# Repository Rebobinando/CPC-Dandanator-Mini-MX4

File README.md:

# CPC Dandanator!Mini MX4

## What is this? Why?

Based on the original design from Dandare - CPC Dandanator!Mini, this design proposes the adoption/integration of MX4 connector instead of the Amstrad CPC standard 50 pin edge connector. This version then fits into the many expansion boards available up to now.

This allows for the CPC expansion boards users to enjoy this hardware, together with rest of accessories without the need of unplugging them.

Original design and complete description are available in the [Dandare Website](http://www.dandare.es/Proyectos_Dandare/CPC_Dandanator%21_Mini.html)

More development details are available in [VadeRetro forum](https://www.va-de-retro.com/foros/viewtopic.php?f=63&t=9113) 

## Features

Additionally to the features available in the original design, I added the additional following ones:

- MX4 connector format to fit into CPC expansion boards.
- CPLD is plugged into a socket for easier soldering process by hand.
- Switch for Enable/Disable the accessory instead of button.
- DIP oscillator instead of SMD one.
- Additional switch to switch on /switch off the board.

CPLD programming is fully compatible with original version available at Dandare website.

EEPROM programming original software is also fully compatible. It is available in Dandare website too.

## Bill of materials

|Qty| Component     | Value               |  Package  |
|---|---------------|---------------------|-----------|
| 3 | Capacitor     | 100nF               | SMD C0805 | 
| 2 | Capacitor     | 10uF                | SMD C0805 |
| 2 | Capacitor     | 22pF                | SMD C0805 |
| 1 | Capacitor     | 10nF                | SMD C0805 |
| 1 | IC            | CH340G              | SOP16     |
| 1 | Voltage Reg   | AMS1117-3.3         | SOT223    |
| 1 | MPF           | SST39SF040          | PLCC32    |
| 1 | CPLD          | XC9572XL            | PLCC44    |
| 1 | Oscillator    | 12 MHz              | HC49S     |
| 3 | Resistor      | 10K                 | R805      |
| 1 | USB plug      | Micro USB Type B    | SMD       |
| 1 | pin           | 1x6                 | DIP       |
| 1 | pin           | 1x2                 | DIP       |
| 2 | Button        | 6x6x9 Right Angle   | DIP       |
| 2 | Switch        | MSK-12D19           | DIP       |
| 1 | MX4 connector | DC3-50P Right Angle | DIP       |
| 1 | Socket        | PLCC32              | DIP       |
| 1 | Socket        | PLCC44              | DIP       |

## Board layout

These are the main elements:

All development of this version has been performed with Eagle 8.6.0. Schematics and Board files are available, as well as Gerber files under below license agreement.

This is the board installed onto the CPC expansion board:

PCB screenshot:

## Warning & Disclaimer
If you want to build yourself, please proceed and read carefully all this information. A guide of assembly is available in VadeRetro forum [here](https://www.va-de-retro.com/foros/viewtopic.php?f=63&t=9113) . Bear in mind that all the information in this project is published in good faith and for general information purpose only. I do not make any warranties about the completeness, reliability, and accuracy of this information. Any action you take upon the information you find here, is strictly at your own risk. I will not be liable for any losses and/or damages. In case of doubts, do not hesitate to ask and I will try to help as far as I can!

## Thanks to

- Dandare and the team for carrying out the original (smart & awesome) design of this interface, for giving permission for use and modification of it, and for giving support during the development.

- All the users for VadeRetro forum, who supported the initial batch of units.

Hope we are all enjoying them!

## Redistribution

All development is Public Domain, as the original one. For latest state, please check at [Dandare website](http://www.dandare.es/Proyectos_Dandare/CPC_Dandanator%21_Mini.html)

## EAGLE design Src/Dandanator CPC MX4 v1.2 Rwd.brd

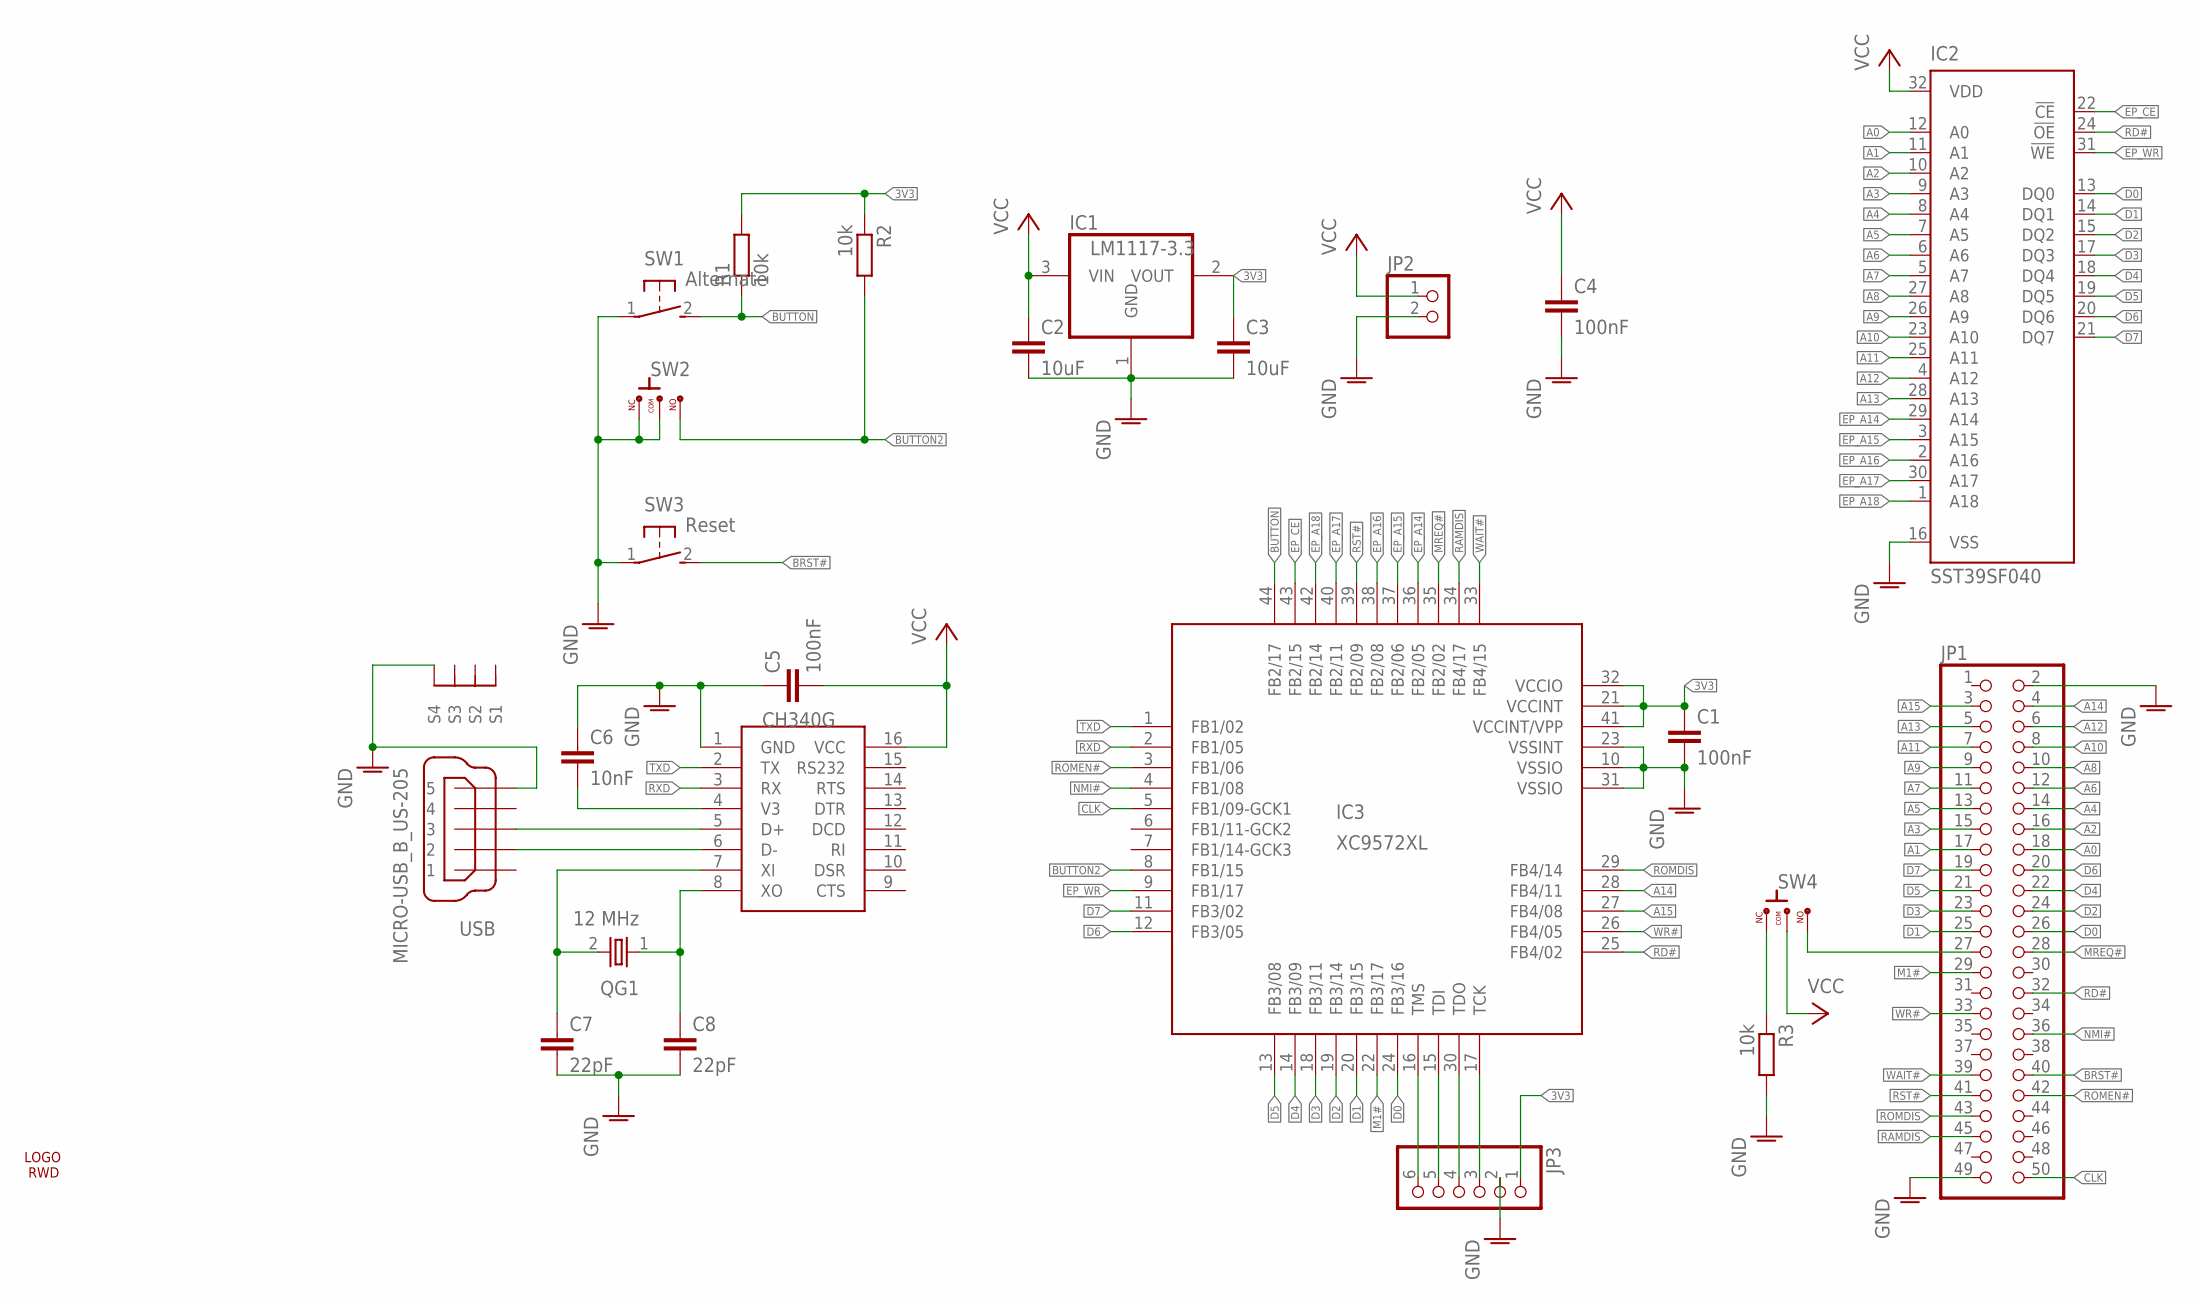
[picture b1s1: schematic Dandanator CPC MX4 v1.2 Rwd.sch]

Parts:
C1, C4, C5: 100nF; C0805
C2, C3: 10uF; C0805
C6: 10nF; C0805
C7, C8: 22pF; C0805
CH340G: CH340G; SOIC16
IC1: LM1117-3.3; SOT223
IC2: SST39SF040; S32
IC3: XC9572XL; S44
JP1: PINHD-2X25; 2X25
JP2: PINHD-1X2; 1X02
JP3: PINHD-1X6; 1X06
QG1: 12 MHz; CRYSTAL_HC49/S
R1, R2, R3: 10k; R0805
SW1: Alternate; B3F-31XX
SW2: Disable; 1P2T-MSK12D19-DIP
SW3: Reset; B3F-31XX
SW4: ON/OFF; 1P2T-MSK12D19-DIP
U$1: LOGO7BOTTOM; LOGO7_SK22
USB: MICRO-USB_B_US-205; MICRO-USB_B_US-205_DIP

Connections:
3V3: C1.1, C3.1, IC1.2 (VOUT), IC3.21 (VCCINT), IC3.32 (VCCIO), IC3.41 (VCCINT/VPP), JP3.1, R1.2, R2.1
A0: IC2.12 (A0), JP1.18
A1: IC2.11 (A1), JP1.17
A2: IC2.10 (A2), JP1.16
A3: IC2.9 (A3), JP1.15
A4: IC2.8 (A4), JP1.14
A5: IC2.7 (A5), JP1.13
A6: IC2.6 (A6), JP1.12
A7: IC2.5 (A7), JP1.11
A8: IC2.27 (A8), JP1.10
A9: IC2.26 (A9), JP1.9
A10: IC2.23 (A10), JP1.8
A11: IC2.25 (A11), JP1.7
A12: IC2.4 (A12), JP1.6
A13: IC2.28 (A13), JP1.5
A14: IC3.28 (FB4/11), JP1.4
A15: IC3.27 (FB4/08), JP1.3
AGND: C1.2, C2.2, C3.2, C4.2, C5.1, C6.1, C7.2, C8.2, CH340G.1 (GND), IC1.1 (GND), IC2.16 (VSS), IC3.10 (VSSIO), IC3.23 (VSSINT), IC3.31 (VSSIO), JP1.2, JP1.49, JP2.2, JP3.2, R3.2, SW1.1, SW2.P$1 (1), SW2.P$2 (2), SW3.1, USB.5, USB.M4 (S4)
BRST#: JP1.40, SW3.2 (S)
BUTTON: IC3.44 (FB2/17), R1.1, SW1.2 (S)
BUTTON2: IC3.8 (FB1/15), R2.2, SW2.P$3 (3)
CLK: IC3.5 (FB1/09-GCK1), JP1.50
D0: IC2.13 (DQ0), IC3.24 (FB3/16), JP1.26
D1: IC2.14 (DQ1), IC3.20 (FB3/15), JP1.25
D2: IC2.15 (DQ2), IC3.19 (FB3/14), JP1.24
D3: IC2.17 (DQ3), IC3.18 (FB3/11), JP1.23
D4: IC2.18 (DQ4), IC3.14 (FB3/09), JP1.22
D5: IC2.19 (DQ5), IC3.13 (FB3/08), JP1.21
D6: IC2.20 (DQ6), IC3.12 (FB3/05), JP1.20
D7: IC2.21 (DQ7), IC3.11 (FB3/02), JP1.19
EP_A14: IC2.29 (A14), IC3.36 (FB2/05)
EP_A15: IC2.3 (A15), IC3.37 (FB2/06)
EP_A16: IC2.2 (A16), IC3.38 (FB2/08)
EP_A17: IC2.30 (A17), IC3.40 (FB2/11)
EP_A18: IC2.1 (A18), IC3.42 (FB2/14)
EP_CE: IC2.22 (!CE), IC3.43 (FB2/15)
EP_WR: IC2.31 (!WE), IC3.9 (FB1/17)
M1#: IC3.22 (FB3/17), JP1.29
MREQ#: IC3.35 (FB2/02), JP1.28
unnamed: IC3.16 (TMS), JP3.6
unnamed: IC3.15 (TDI), JP3.5
unnamed: IC3.30 (TDO), JP3.4
unnamed: IC3.17 (TCK), JP3.3
unnamed: JP1.27, SW4.P$3 (3)
unnamed: C6.2, CH340G.4 (V3)
unnamed: CH340G.6 (D-), USB.2
unnamed: CH340G.5 (D+), USB.3
unnamed: C8.1, CH340G.8 (XO), QG1.1
unnamed: C7.1, CH340G.7 (XI), QG1.2
unnamed: R3.1, SW4.P$1 (1)
NMI#: IC3.4 (FB1/08), JP1.36
RAMDIS: IC3.34 (FB4/17), JP1.45
RD#: IC2.24 (!OE), IC3.25 (FB4/02), JP1.32
ROMDIS: IC3.29 (FB4/14), JP1.43
ROMEN#: IC3.3 (FB1/06), JP1.42
RST#: IC3.39 (FB2/09), JP1.41
RXD: CH340G.3 (RX), IC3.2 (FB1/05)
TXD: CH340G.2 (TX), IC3.1 (FB1/02)
VCC: C2.1, C4.1, C5.2, CH340G.16 (VCC), IC1.3 (VIN), IC2.32 (VDD), JP2.1, SW4.P$2 (2)
WAIT#: IC3.33 (FB4/15), JP1.39
WR#: IC3.26 (FB4/05), JP1.33

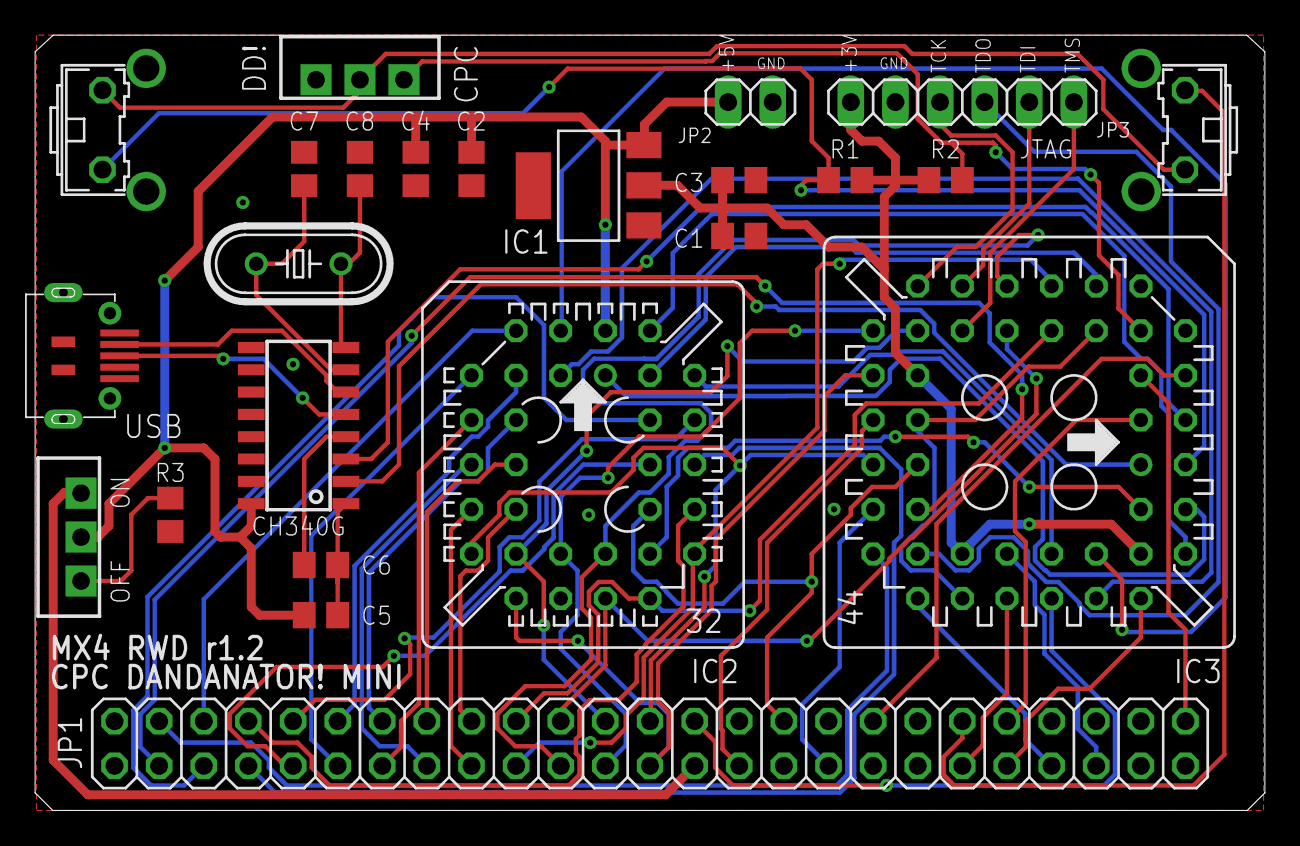
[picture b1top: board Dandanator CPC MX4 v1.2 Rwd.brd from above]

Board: 2 copper layers, 70.0 x 44.1 mm, 25 parts (0 on the bottom side), 61 nets.
